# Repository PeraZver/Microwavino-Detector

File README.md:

# Microwavino Detector
RSSI Detector &amp; Coupler for Microwavino. Based on 1 MHz - 10 GHz log detector AD8319 and [Henrik's stripline coupler](http://hforsten.com/cheap-homemade-30-mhz-6-ghz-vector-network-analyzer.html#Directional-coupler). 

Project development details available at [Hackaday.io](https://hackaday.io/project/27190-microwavino)

Pero, September 2017

[Helentronica](https://www.helentronica.com)

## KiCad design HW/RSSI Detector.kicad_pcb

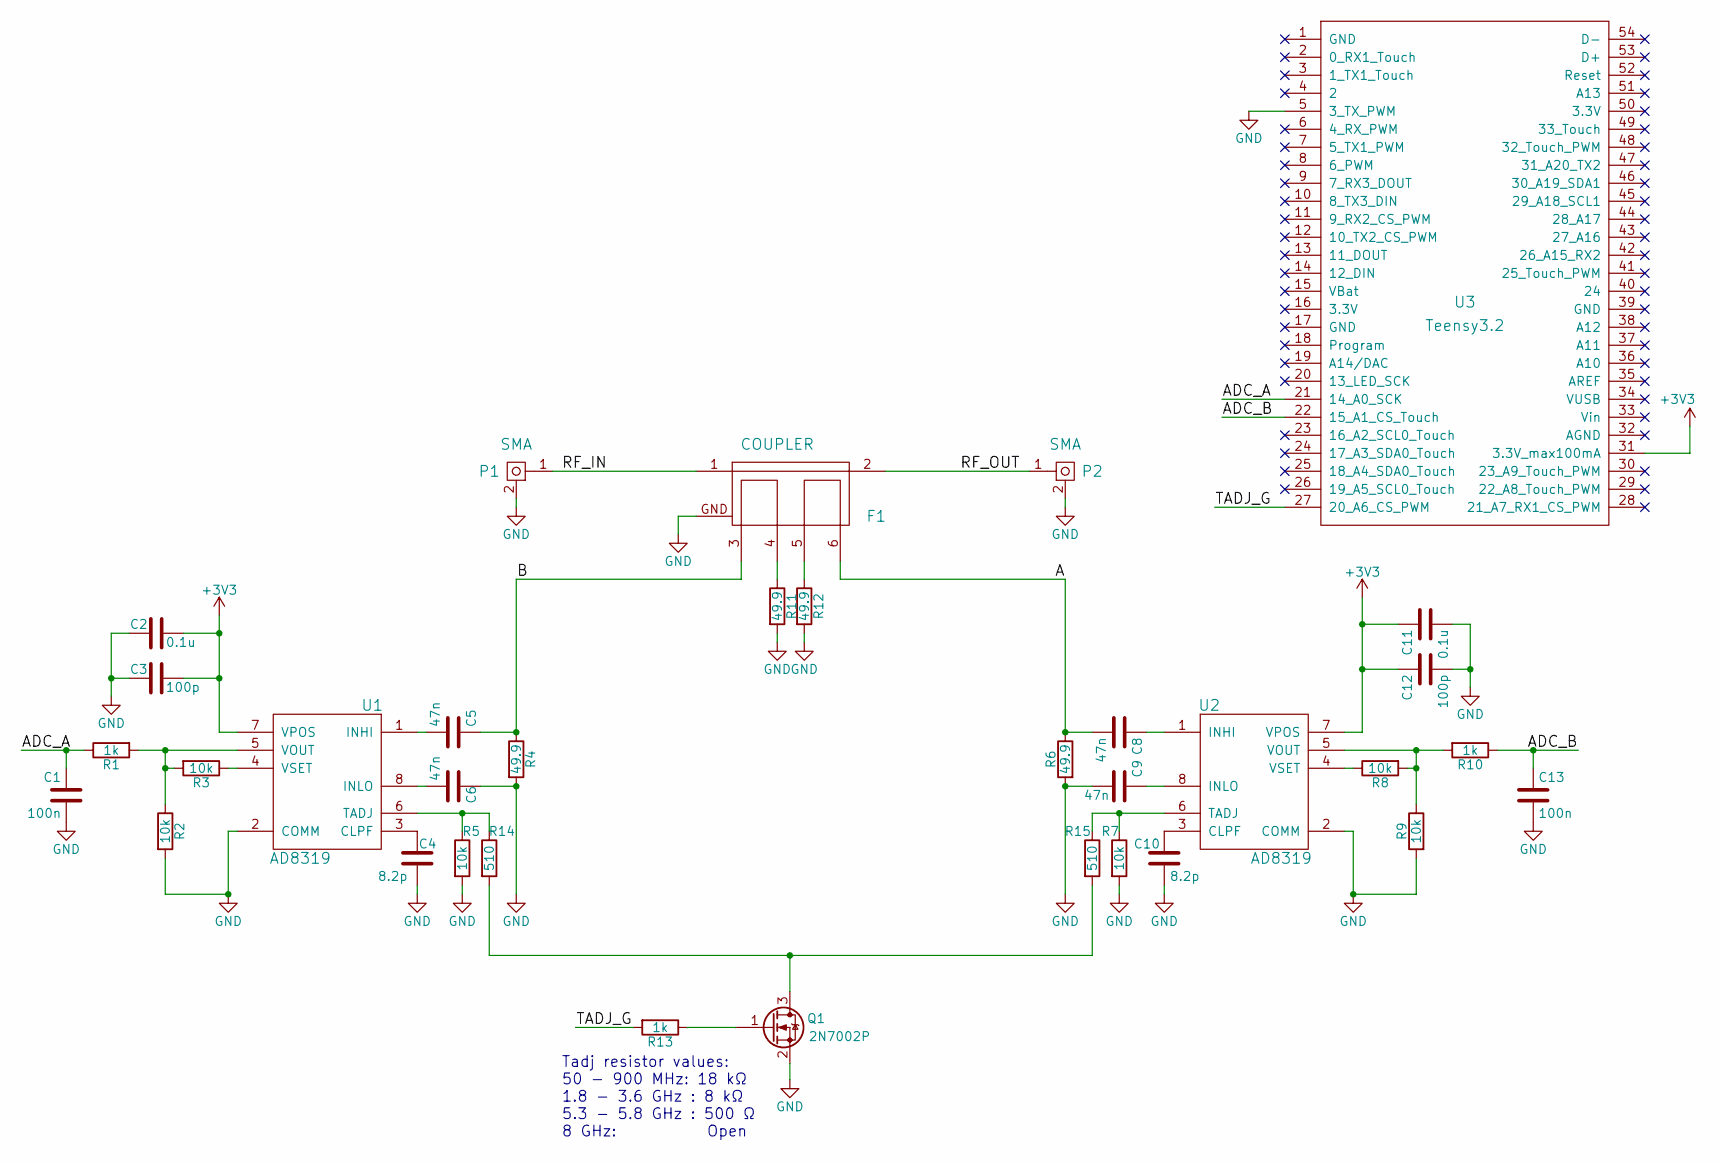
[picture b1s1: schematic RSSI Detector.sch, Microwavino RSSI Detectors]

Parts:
C1, C13: 100n; C_0603b
C2, C11: 0.1u; C_0603b
C3, C12: 100p; C_0603b
C4, C10: 8.2p; C_0603b
C5, C6, C8, C9: 47n; C_0402b
F1: COUPLER; coupler4
P1, P2: SMA; CONSMA003.062
Q1: 2N7002P; SOT-23
R1, R10, R13: 1k; R_0603
R2, R3, R5, R7, R8, R9: 10k; R_0603
R4, R6, R11, R12: 49.9; R_0402b
R14, R15: 510; R_0603
U1, U2: AD8319; 8-LFCSP_VD
U3: Teensy3.2; Teensy30_31_32_LC_modified

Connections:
+3V3: C2.1, C3.1, C11.1, C12.1, U1.7 (VPOS), U2.7 (VPOS), U3.31 (3.3V_max100mA)
/A: C8.2, F1.6, R6.1
/ADC_A: C1.1, R1.1, U3.21 (14_A0_SCK)
/ADC_B: C13.1, R10.1, U3.22 (15_A1_CS_Touch)
/B: C5.1, F1.3, R4.1
/RF_IN: F1.1, P1.1; also elsewhere on the board
/RF_OUT: F1.2, P2.1; also elsewhere on the board
/TADJ_G: R13.2, U3.27 (20_A6_CS_PWM)
GND: C1.2, C2.2, C3.2, C4.1, C6.1, C9.2, C10.1, C11.2, C12.2, C13.2, F1.GND, P1.2, P2.2, Q1.2 (S), R2.2, R4.2, R5.2, R6.2, R7.2, R9.2, R11.2, R12.2, U1.2 (COMM), U2.2 (COMM), U3.5 (3_TX_PWM); also elsewhere on the board
unnamed: C4.2, U1.3 (CLPF)
unnamed: C5.2, U1.1 (INHI)
unnamed: C6.2, U1.8 (INLO)
unnamed: C8.1, U2.1 (INHI)
unnamed: C9.1, U2.8 (INLO)
unnamed: C10.2, U2.3 (CLPF)
unnamed: F1.4, R11.1
unnamed: F1.5, R12.1
unnamed: Q1.1 (G), R13.1
unnamed: Q1.3 (D), R14.2, R15.2
unnamed: R1.2, R2.1, R3.2, U1.5 (VOUT)
unnamed: R3.1, U1.4 (VSET)
unnamed: R8.1, U2.4 (VSET)
unnamed: R8.2, R9.1, R10.2, U2.5 (VOUT)
unnamed: R5.1, R14.1, U1.6 (TADJ)
unnamed: R7.1, R15.1, U2.6 (TADJ)

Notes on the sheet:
Tadj resistor values: 50 - 900 MHz: 18 kΩ 1.8 - 3.6 GHz : 8 kΩ 5.3 - 5.8 GHz : 500 Ω 8 GHz: Open

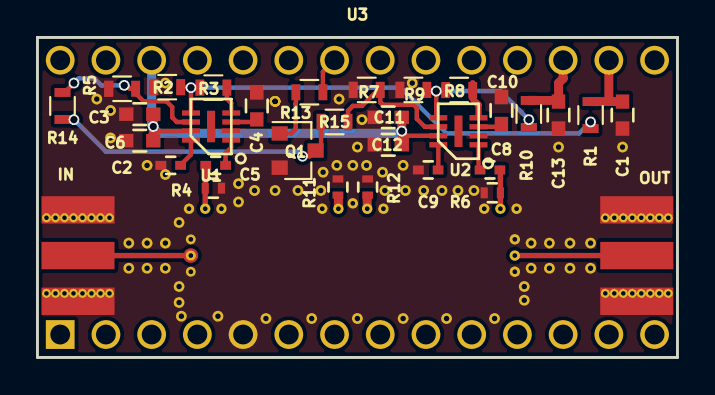
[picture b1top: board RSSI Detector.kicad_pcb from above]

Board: 4 copper layers, 35.6 x 17.8 mm, 34 parts (0 on the bottom side), 25 nets.

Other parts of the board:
IN: SMA; CONSMA003.062
OUT: SMA; CONSMA003.062

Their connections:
/RF_IN: IN.1; also elsewhere on the board
/RF_OUT: OUT.1; also elsewhere on the board
GND: IN.2, OUT.2; also elsewhere on the board

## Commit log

2017-09-20 initial commit, sch started
2017-09-20 finished sch, footprints done
2017-09-27 prelim placement
2017-09-27 layout finished
2017-09-27 3d models finished
2017-09-27 put Henrik's coupler
2017-09-27 layout done
2017-09-28 fixed problems with 3d
2017-09-28 fixed readme
2017-09-28 added images
2017-09-28 layout almost complete
2017-09-28 layout complete
2017-09-28 added temp adj transistor switch
2017-09-28 released and ordered
